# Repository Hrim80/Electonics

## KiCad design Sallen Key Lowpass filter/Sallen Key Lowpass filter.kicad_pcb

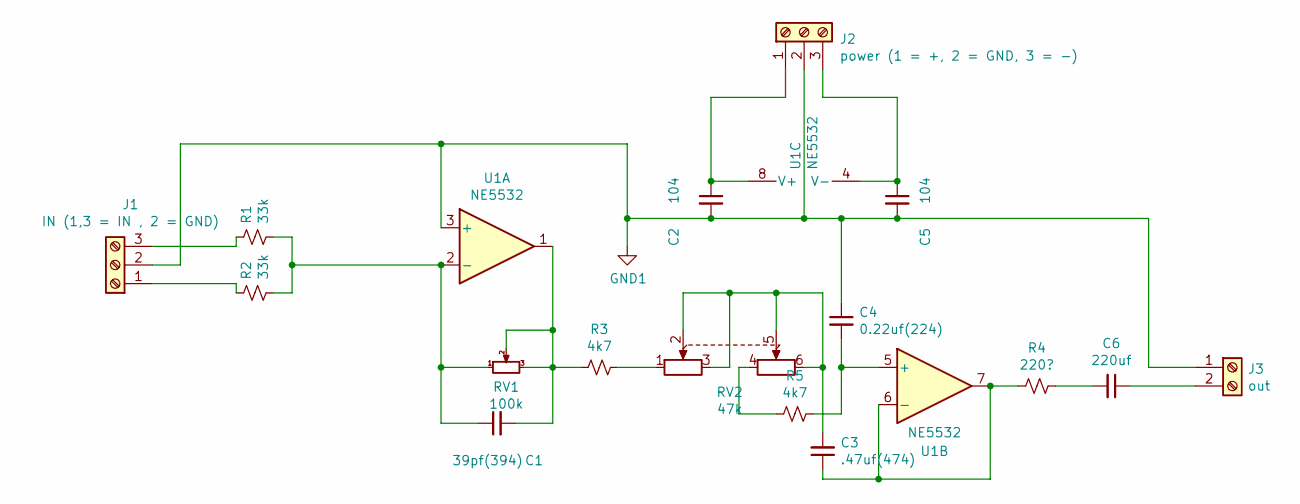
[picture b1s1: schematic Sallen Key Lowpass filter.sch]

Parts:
C1: 39pf(394); C_Disc_D5.1mm_W3.2mm_P5.00mm
C2, C5: 104; C_Disc_D5.1mm_W3.2mm_P5.00mm
C3: .47uf(474); C_Disc_D5.1mm_W3.2mm_P5.00mm
C4: 0.22uf(224); C_Disc_D5.1mm_W3.2mm_P5.00mm
C6: 220uf; CP_Radial_D8.0mm_P3.50mm
J1: IN (1,3 = IN , 2 = GND); TerminalBlock_bornier-3_P5.08mm
J2: power (1 = +, 2 = GND, 3 = -); TerminalBlock_bornier-3_P5.08mm
J3: out; TerminalBlock_bornier-2_P5.08mm
R1, R2: 33k; R_Axial_DIN0207_L6.3mm_D2.5mm_P10.16mm_Horizontal
R3, R5: 4k7; R_Axial_DIN0207_L6.3mm_D2.5mm_P10.16mm_Horizontal
R4: 220?; R_Axial_DIN0207_L6.3mm_D2.5mm_P10.16mm_Horizontal
RV1: 100k; Potentiometer_Alps_RK163_Single_Horizontal
RV2: 47k; Potentiometer_Alps_RK163_Dual_Horizontal
U1: NE5532; DIP-8_W7.62mm_Socket_LongPads

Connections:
GND1: C2.2, C4.1, C5.2, J1.2, J2.2, J3.1, U1.3 (+)
unnamed: C1.1, R1.2, R2.2, RV1.1, U1.2 (-)
unnamed: C1.2, R3.1, RV1.2, RV1.3, U1.1
unnamed: C2.1, J2.1, U1.8 (V+)
unnamed: C3.1, R4.1, U1.6 (-), U1.7
unnamed: C3.2, RV2.2, RV2.3, RV2.5, RV2.6
unnamed: C4.2, R5.1, U1.5 (+)
unnamed: C5.1, J2.3, U1.4 (V-)
unnamed: C6.1, J3.2
unnamed: C6.2, R4.2
unnamed: J1.1, R2.1
unnamed: J1.3, R1.1
unnamed: R3.2, RV2.1
unnamed: R5.2, RV2.4

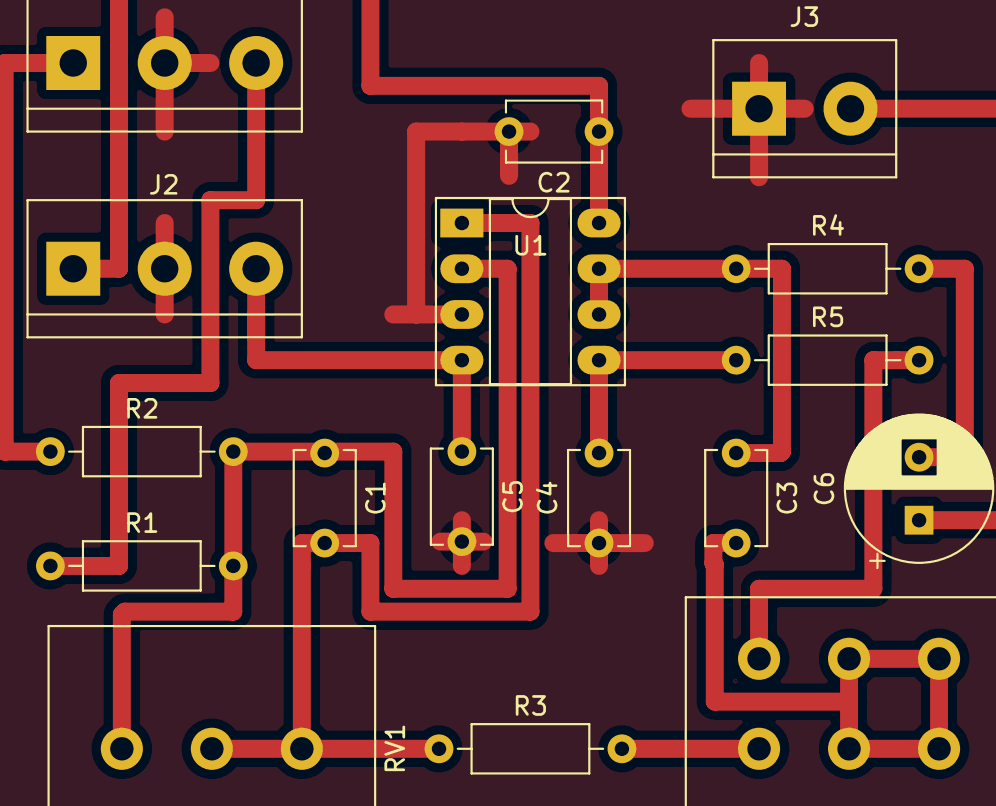
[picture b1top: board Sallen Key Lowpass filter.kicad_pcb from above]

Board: 2 copper layers, 17 parts (0 on the bottom side), 14 nets.

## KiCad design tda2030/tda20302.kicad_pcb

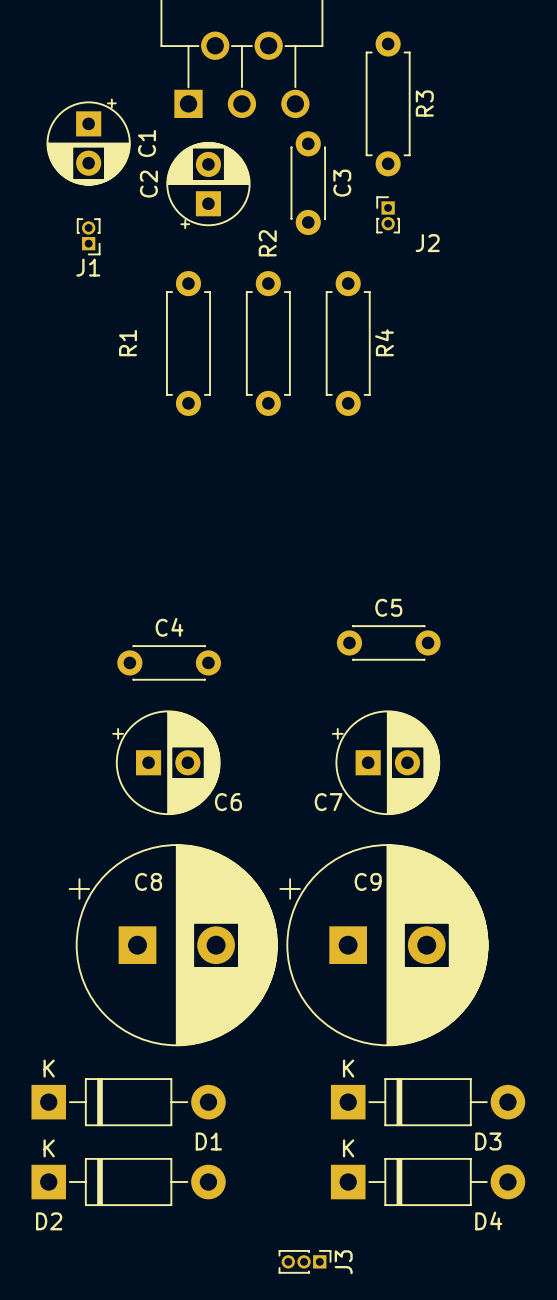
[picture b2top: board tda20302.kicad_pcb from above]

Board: 2 copper layers, 21 parts (0 on the bottom side), 11 nets, no tracks yet.

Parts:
C1: 1uf; CP_Radial_D5.0mm_P2.50mm
C2: 22uf; CP_Radial_D5.0mm_P2.50mm
C3: 103; C_Disc_D4.3mm_W1.9mm_P5.00mm
C4, C5: 104; C_Disc_D4.3mm_W1.9mm_P5.00mm
C6, C7: 100uf; CP_Radial_D6.3mm_P2.50mm
C8, C9: 2000uf; CP_Radial_D12.5mm_P5.00mm
D1, D2, D3, D4: 1N4007; D_DO-41_SOD81_P10.16mm_Horizontal
J1: Ain; PinHeader_1x02_P1.00mm_Vertical
J2: Aout; PinHeader_1x02_P1.00mm_Vertical
J3: Pin; PinHeader_1x03_P1.00mm_Vertical
R1, R3: 22k; R_Axial_DIN0207_L6.3mm_D2.5mm_P7.62mm_Horizontal
R2: 680?; R_Axial_DIN0207_L6.3mm_D2.5mm_P7.62mm_Horizontal
R4: 10?; R_Axial_DIN0207_L6.3mm_D2.5mm_P7.62mm_Horizontal
U1: TDA2030; TO-220-5_P3.4x3.7mm_StaggerOdd_Lead3.8mm_Vertical

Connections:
GND: C4.1, C5.2, C6.1, C7.2, C8.1, C9.2, J1.1, J2.2, R1.2, R2.2, R4.2
unnamed: C1.1, R1.1, U1.1
unnamed: C1.2, J1.2
unnamed: C2.1, R3.2, U1.2
unnamed: C2.2, R2.1
unnamed: C3.1, J2.1, R3.1, U1.4
unnamed: C3.2, R4.1
unnamed: C4.2, C6.2, C8.2, D1.2, D2.2, U1.3
unnamed: C5.1, C7.1, C9.1, D3.1, D4.1, U1.5
unnamed: D1.1, D4.2, J3.1
unnamed: D2.1, D3.2, J3.2
